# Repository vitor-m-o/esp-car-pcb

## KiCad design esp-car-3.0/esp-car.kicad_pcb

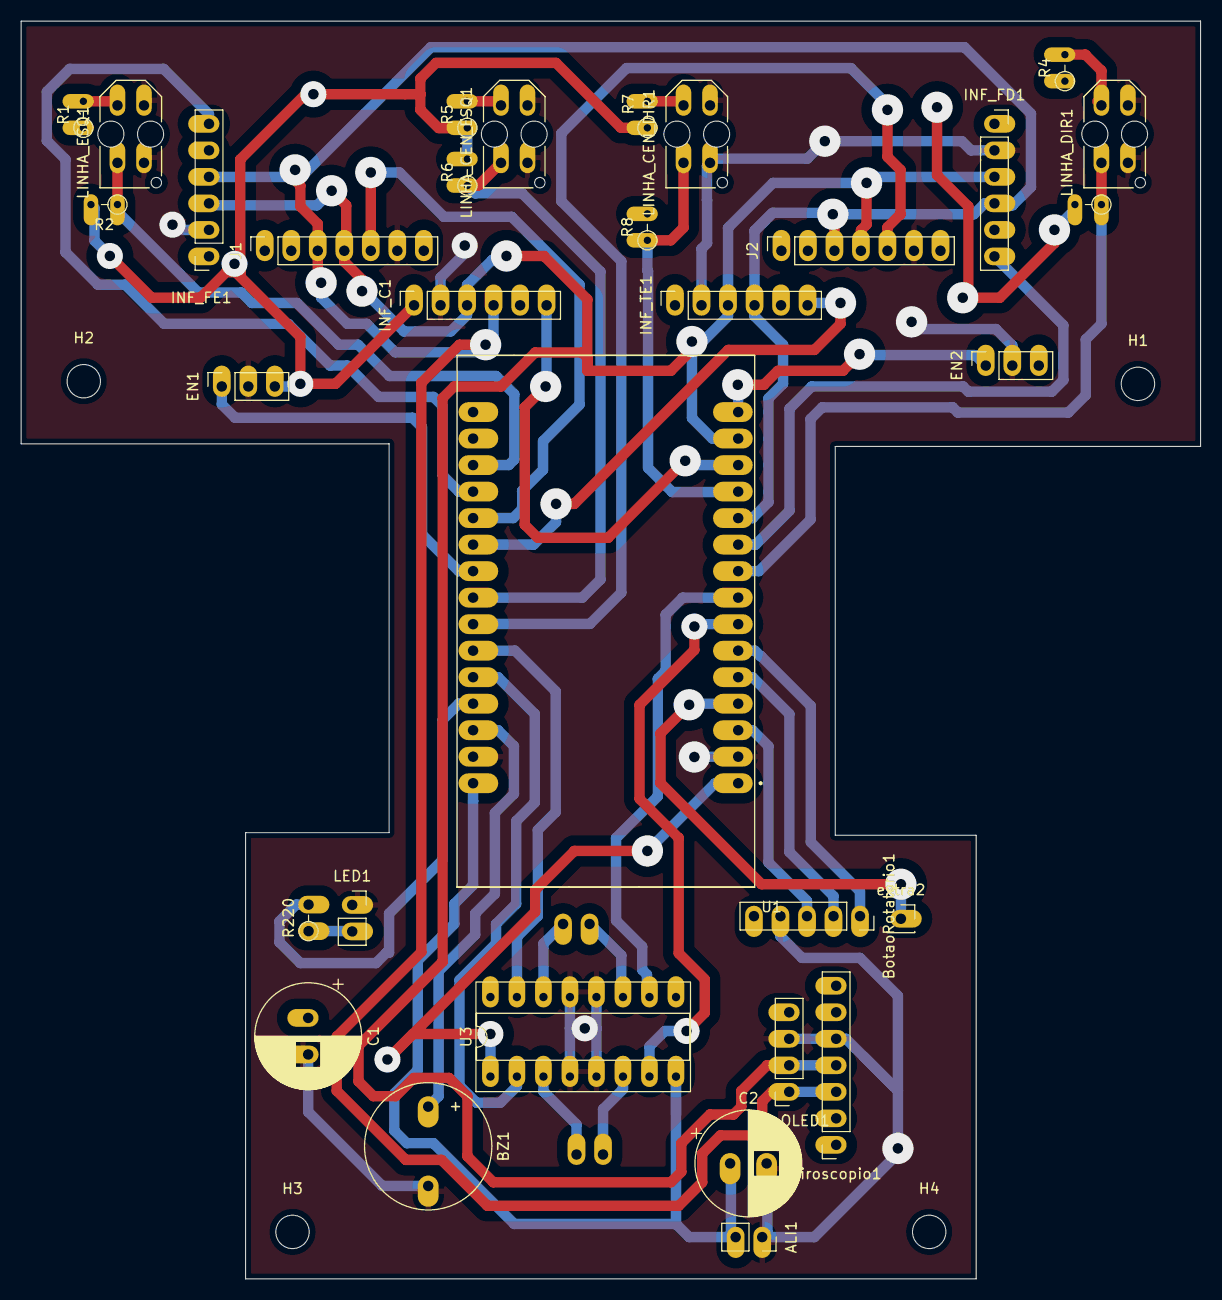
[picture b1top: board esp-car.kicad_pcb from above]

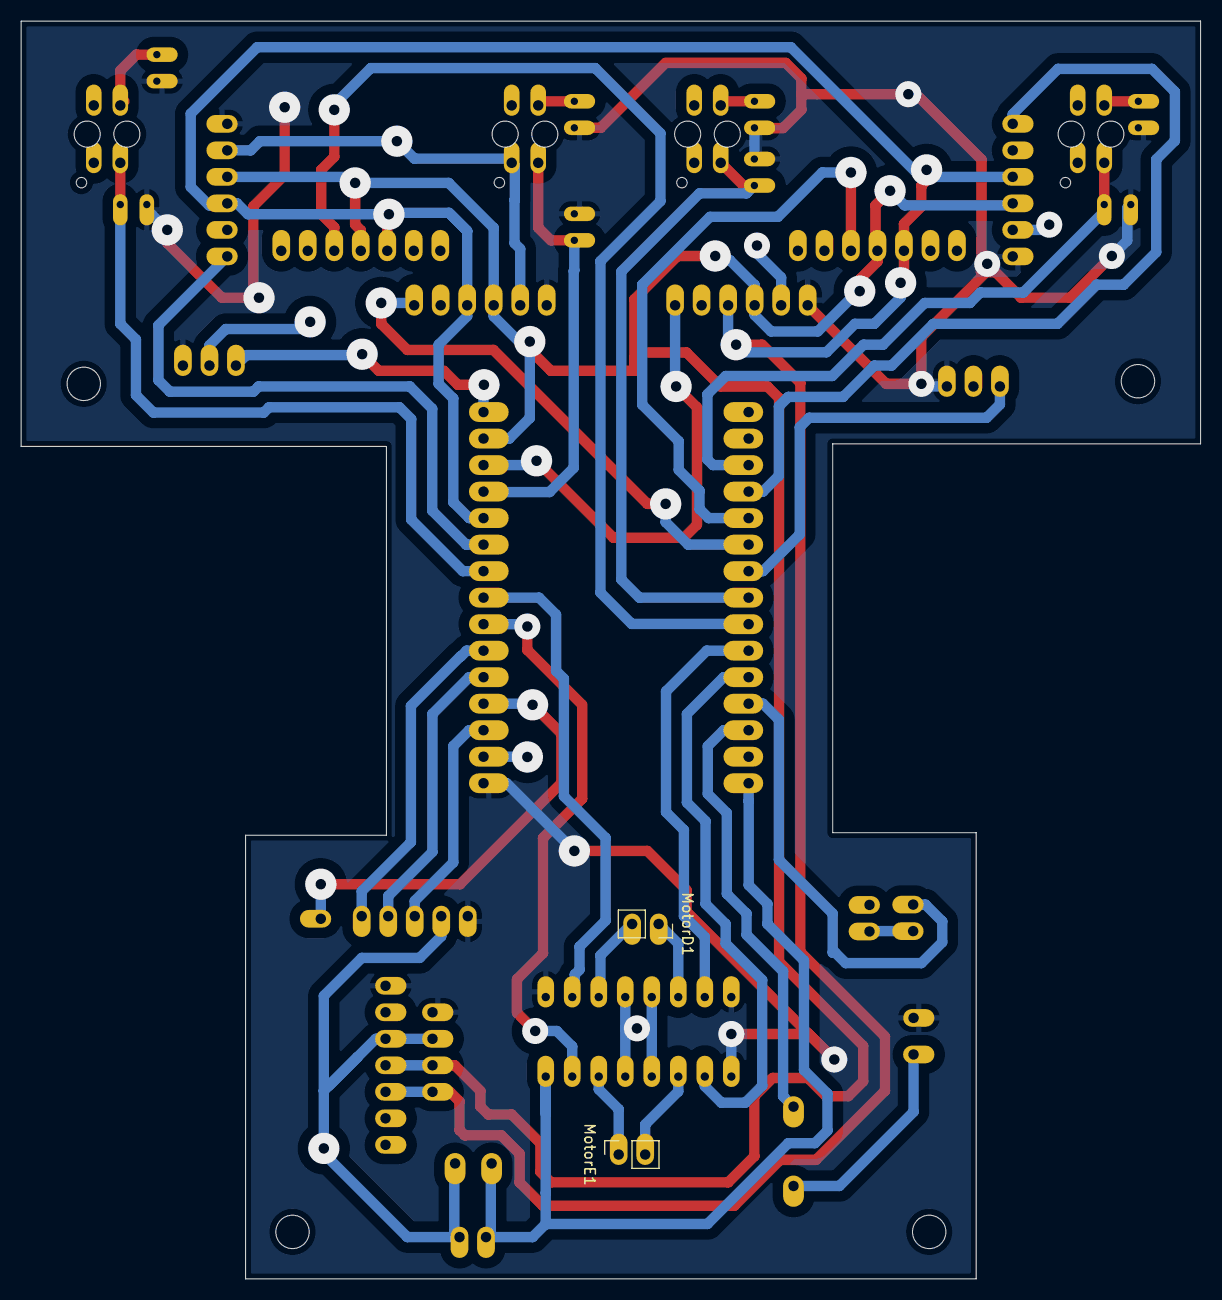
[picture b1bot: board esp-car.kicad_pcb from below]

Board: 2 copper layers, 113.0 x 120.5 mm, 38 parts (2 on the bottom side), 36 nets.

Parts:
ALI1: Conn_01x02_Socket; PinSocket_1x02_P2.54mm_Vertical
BZ1: Buzzer; Buzzer_12x9.5RM7.6
BotaoRotatorio1: Conn_01x05_Socket; PinSocket_1x05_P2.54mm_Vertical
C1, C2: C; CP_Radial_D10.0mm_P3.50mm
EN1, EN2: Conn_01x03_Socket; PinSocket_1x03_P2.54mm_Vertical
H1, H2, H3, H4: MountingHole; MountingHole_3.2mm_M3
INF_C1: Conn_01x06_Socket; PinSocket_1x06_P2.54mm_Vertical
INF_FD1: Conn_01x06_Socket; PinSocket_1x06_P2.54mm_Vertical
INF_FE1: Conn_01x06_Socket; PinSocket_1x06_P2.54mm_Vertical
INF_TE1: Conn_01x06_Socket; PinSocket_1x06_P2.54mm_Vertical
J1, J2: Conn_01x07_Socket; PinSocket_1x07_P2.54mm_Vertical
LED1: Conn_01x02_Socket; PinSocket_1x02_P2.54mm_Vertical
LINHA_CEN_DIR1: OPTO_TCRT5000
LINHA_CEN_ESQ1: OPTO_TCRT5000
LINHA_DIR1: OPTO_TCRT5000
LINHA_ESQ1: LINHA_ESQ; OPTO_TCRT5000
MotorD1: Conn_01x02_Socket; PinSocket_1x02_P2.54mm_Vertical
MotorE1: Conn_01x02_Socket; PinSocket_1x02_P2.54mm_Vertical
R1, R4, R5, R7: 150; R_Axial_DIN0204_L3.6mm_D1.6mm_P2.54mm_Vertical
R2, R3, R6, R8: 10K; R_Axial_DIN0204_L3.6mm_D1.6mm_P2.54mm_Vertical
R220: R; R_Axial_DIN0204_L3.6mm_D1.6mm_P2.54mm_Vertical
TelaOLED1: Conn_01x04_Socket; PinSocket_1x04_P2.54mm_Vertical
U1: ESP32-DEVKIT-V1; MODULE_ESP32_DEVKIT_V1_30_PIN
U3: L293D; CERDIP-16_W7.62mm_SideBrazed_LongPads_Socket
extra2: Conn_01x01_Socket; PinSocket_1x01_P2.54mm_Vertical
giroscopio1: Conn_01x07_Socket; PinSocket_1x07_P2.54mm_Vertical

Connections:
2: U1.4 (D2), extra2.1
3v3: BotaoRotatorio1.5, C1.1, EN1.3, EN2.3, INF_C1.1, INF_FD1.1, INF_FE1.1, INF_TE1.1, R1.1, R2.2, R3.2, R4.1, R5.1, R6.2, R7.1, R8.2, TelaOLED1.4, U1.1 (3V3), U3.1 (EN1,2), U3.9 (EN3,4), U3.16 (VCC1), giroscopio1.7
BUZZ: BZ1.1 (+), U1.28 (D13)
C1: J1.5, U1.20 (D35)
C2: J2.5, U1.24 (D26)
CD: LINHA_CEN_DIR1.COLL, R8.1, U1.12 (RX0)
CE: LINHA_CEN_ESQ1.COLL, R6.1, U1.23 (D25)
GND: ALI1.1, BZ1.2 (-), BotaoRotatorio1.4, C1.2, C2.2, EN1.2, EN2.2, INF_C1.2, INF_FD1.2, INF_FE1.2, INF_TE1.2, J1.6, J2.6, LED1.1, LINHA_CEN_DIR1.CATH, LINHA_CEN_DIR1.E, LINHA_CEN_ESQ1.CATH, LINHA_CEN_ESQ1.E, LINHA_DIR1.CATH, LINHA_DIR1.E, LINHA_ESQ1.CATH, LINHA_ESQ1.E, TelaOLED1.3, U1.2 (GND), U1.29 (GND), U3.4 (GND), U3.5 (GND), U3.12 (GND), U3.13 (GND), giroscopio1.5
IN1: U1.26 (D14), U3.2 (1A)
IN2: U1.7 (TX2), U3.7 (2A)
IN3: U1.8 (D5), U3.10 (3A)
IN4: U1.25 (D27), U3.15 (4A)
INF_C: INF_C1.6, U1.13 (TX0)
INF_FD: INF_FD1.6, U1.10 (D19)
INF_FE: INF_FE1.6, U1.19 (D34)
INF_TD: INF_TE1.6, U1.21 (D32)
KEY: BotaoRotatorio1.1, U1.6 (RX2)
LD: LINHA_DIR1.COLL, R3.1, U1.9 (D18)
LE: LINHA_ESQ1.COLL, R2.1, U1.18 (VN)
LED: R220.2, U1.27 (D12)
unnamed: LED1.2, R220.1
unnamed: LINHA_CEN_DIR1.A, R7.2
unnamed: LINHA_CEN_ESQ1.A, R5.2
unnamed: LINHA_DIR1.A, R4.2
unnamed: LINHA_ESQ1.A, R1.2
OUT1: MotorE1.2, U3.3 (1Y)
OUT2: MotorE1.1, U3.6 (2Y)
OUT3: MotorD1.2, U3.11 (3Y)
OUT4: MotorD1.1, U3.14 (4Y)
OUTD: EN2.1, U1.15 (D23)
OUTE: EN1.1, U1.22 (D33)
S1: BotaoRotatorio1.3, U1.3 (D15)
S2: BotaoRotatorio1.2, U1.5 (D4)
SCL: INF_C1.3, INF_FD1.3, INF_FE1.3, INF_TE1.3, J1.4, J2.4, TelaOLED1.2, U1.14 (D22), giroscopio1.4
SDA: INF_C1.4, INF_FD1.4, INF_FE1.4, INF_TE1.4, J1.3, J2.3, TelaOLED1.1, U1.11 (D21), giroscopio1.3
VIN: ALI1.2, C2.1, U1.30 (VIN), U3.8 (VCC2)

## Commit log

2025-09-30 arquivos pcb
    arquivos pcb
2025-09-30 esp_car 3.1
    30/09 1:06
2025-09-30 .
    .
2025-09-30 esp_car 3.1
2025-09-30 esp-car 3.2
    trilhas de cimas feitas, precisa arrumar resistores
2025-09-30 esp-car 3.3
    furação mais metade da parte de baixo completa
2025-10-01 esp_car_3.0_versao 1
2025-10-01 finalizado, tem que revisar, esp_car_3.3
    revisa os pinos e muda, trabalhe com o stevan vitor
2025-10-02 finalizada agora
2025-10-02 versão finalizada e polida
    muitas alterações
2025-11-05 espcar newvember
    modelo quadradao
